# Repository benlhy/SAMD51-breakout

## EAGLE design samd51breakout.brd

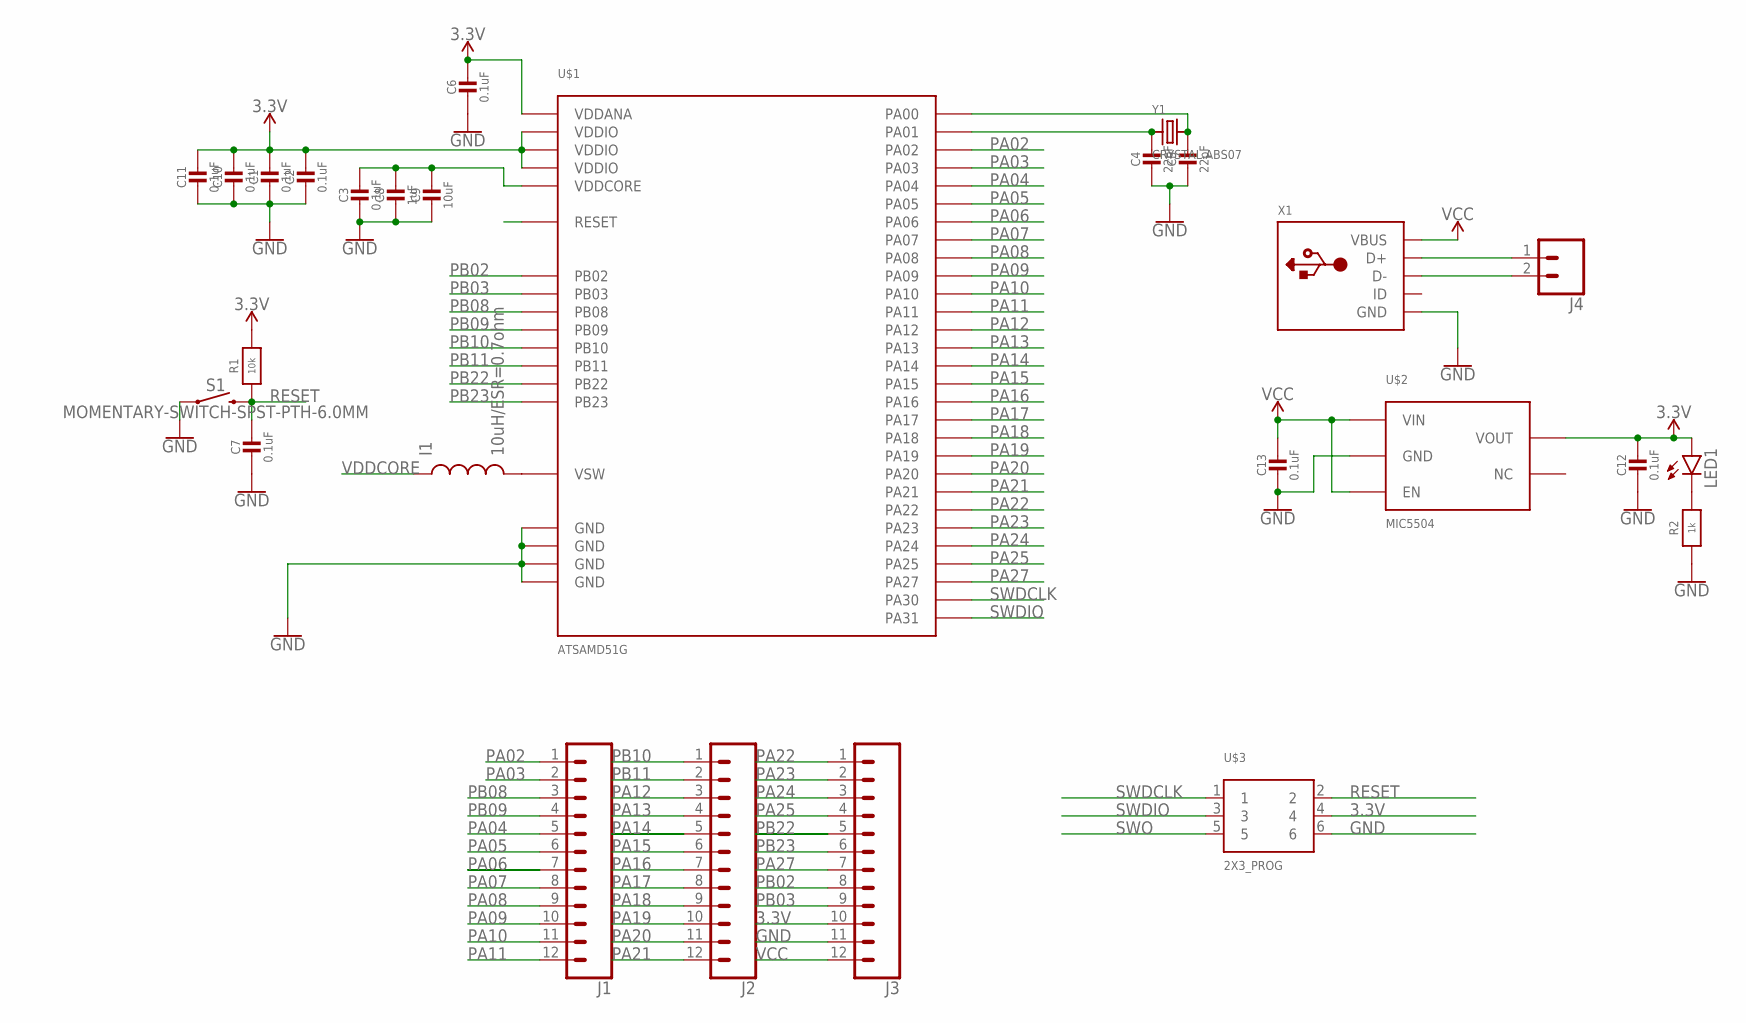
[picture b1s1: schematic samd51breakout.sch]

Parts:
C1, C2, C3, C6, C7, C10, C11, C12, C13: 0.1uF; _0603MP
C4, C5: 22pF; _0603MP
C8: 1uF; _0603MP
C9: 10uF; _0603MP
I1: 10uH/ESR=0.7ohm; 0805
J1, J2, J3: CONN_12; 1X12
J4: CONN_02; 1X02
LED1: LED0603; LED-0603
R1: 10k; _0603MP
R2: 1k; _0603MP
S1: MOMENTARY-SWITCH-SPST-PTH-6.0MM; TACTILE_SWITCH_PTH_6.0MM
U$1: ATSAMD51G; QFN-48
U$2: MIC5504; SOT23-5
U$3: 2X3_PROG; 2X3-SMD_PROG
X1: MICROBUILDER_USB_MICRO_20329_V2; MICROBUILDER_4UCONN_20329_V2
Y1: CRYSTAL.ABS07; ABS07

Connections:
3.3V: C1.1, C2.1, C6.1, C10.1, C11.1, C12.1, J3.10, LED1.A, R1.2, U$1.6 (VDDANA), U$1.17 (VDDIO), U$1.36 (VDDIO), U$1.44 (VDDIO), U$2.5 (VOUT), U$3.4
GND: C1.2, C2.2, C3.2, C4.2, C5.2, C6.2, C7.2, C8.2, C9.2, C10.2, C11.2, C12.2, C13.2, J3.11, R2.1, S1.1, U$1.5 (GND), U$1.18 (GND), U$1.35 (GND), U$1.42 (GND), U$2.2 (GND), U$3.6, X1.BASE@1 (GND), X1.BASE@2 (GND), X1.GND, X1.SPRT@1 (GND), X1.SPRT@2 (GND), X1.SPRT@3 (GND), X1.SPRT@4 (GND)
unnamed: I1.2, U$1.43 (VSW)
unnamed: LED1.C, R2.2
unnamed: C4.1, U$1.2 (PA01), Y1.1
unnamed: C5.1, U$1.1 (PA00), Y1.2
unnamed: J4.1, X1.D+
unnamed: J4.2, X1.D-
PA02: J1.1, U$1.3 (PA02)
PA03: J1.2, U$1.4 (PA03)
PA04: J1.5, U$1.9 (PA04)
PA05: J1.6, U$1.10 (PA05)
PA06: J1.7, U$1.11 (PA06)
PA07: J1.8, U$1.12 (PA07)
PA08: J1.9, U$1.13 (PA08)
PA09: J1.10, U$1.14 (PA09)
PA10: J1.11, U$1.15 (PA10)
PA11: J1.12, U$1.16 (PA11)
PA12: J2.3, U$1.21 (PA12)
PA13: J2.4, U$1.22 (PA13)
PA14: J2.5, U$1.23 (PA14)
PA15: J2.6, U$1.24 (PA15)
PA16: J2.7, U$1.25 (PA16)
PA17: J2.8, U$1.26 (PA17)
PA18: J2.9, U$1.27 (PA18)
PA19: J2.10, U$1.28 (PA19)
PA20: J2.11, U$1.29 (PA20)
PA21: J2.12, U$1.30 (PA21)
PA22: J3.1, U$1.31 (PA22)
PA23: J3.2, U$1.32 (PA23)
PA24: J3.3, U$1.33 (PA24)
PA25: J3.4, U$1.34 (PA25)
PA27: J3.7, U$1.39 (PA27)
PB02: J3.8, U$1.47 (PB02)
PB03: J3.9, U$1.48 (PB03)
PB08: J1.3, U$1.7 (PB08)
PB09: J1.4, U$1.8 (PB09)
PB10: J2.1, U$1.19 (PB10)
PB11: J2.2, U$1.20 (PB11)
PB22: J3.5, U$1.37 (PB22)
PB23: J3.6, U$1.38 (PB23)
RESET: C7.1, R1.1, S1.3 (2), U$1.40 (RESET), U$3.2
SWDCLK: U$1.45 (PA30), U$3.1
SWDIO: U$1.46 (PA31), U$3.3
SWO: U$3.5
VCC: C13.1, J3.12, U$2.1 (VIN), U$2.3 (EN), X1.VBUS
VDDCORE: C3.1, C8.1, C9.1, I1.1, U$1.41 (VDDCORE)

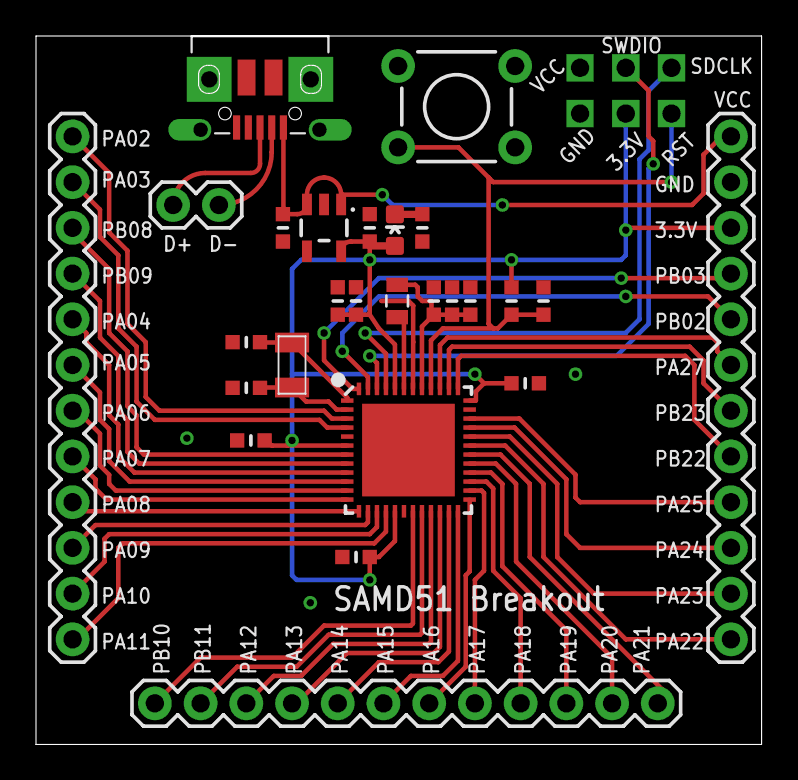
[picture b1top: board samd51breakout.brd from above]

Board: 2 copper layers, 40.3 x 39.4 mm, 27 parts (0 on the bottom side), 46 nets.

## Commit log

2018-07-02 Update to fix mislabelling

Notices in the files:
parts and their libraries:
SparkFun-Connectors: Licensing: Creative Commons ShareAlike 4.0 International - https://creativecommons.org/licenses/by-sa/4.0
